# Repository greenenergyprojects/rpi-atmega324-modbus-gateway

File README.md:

# rpi-atmega324-modbus-gateway
Modbus Gateway for Raspberry PI

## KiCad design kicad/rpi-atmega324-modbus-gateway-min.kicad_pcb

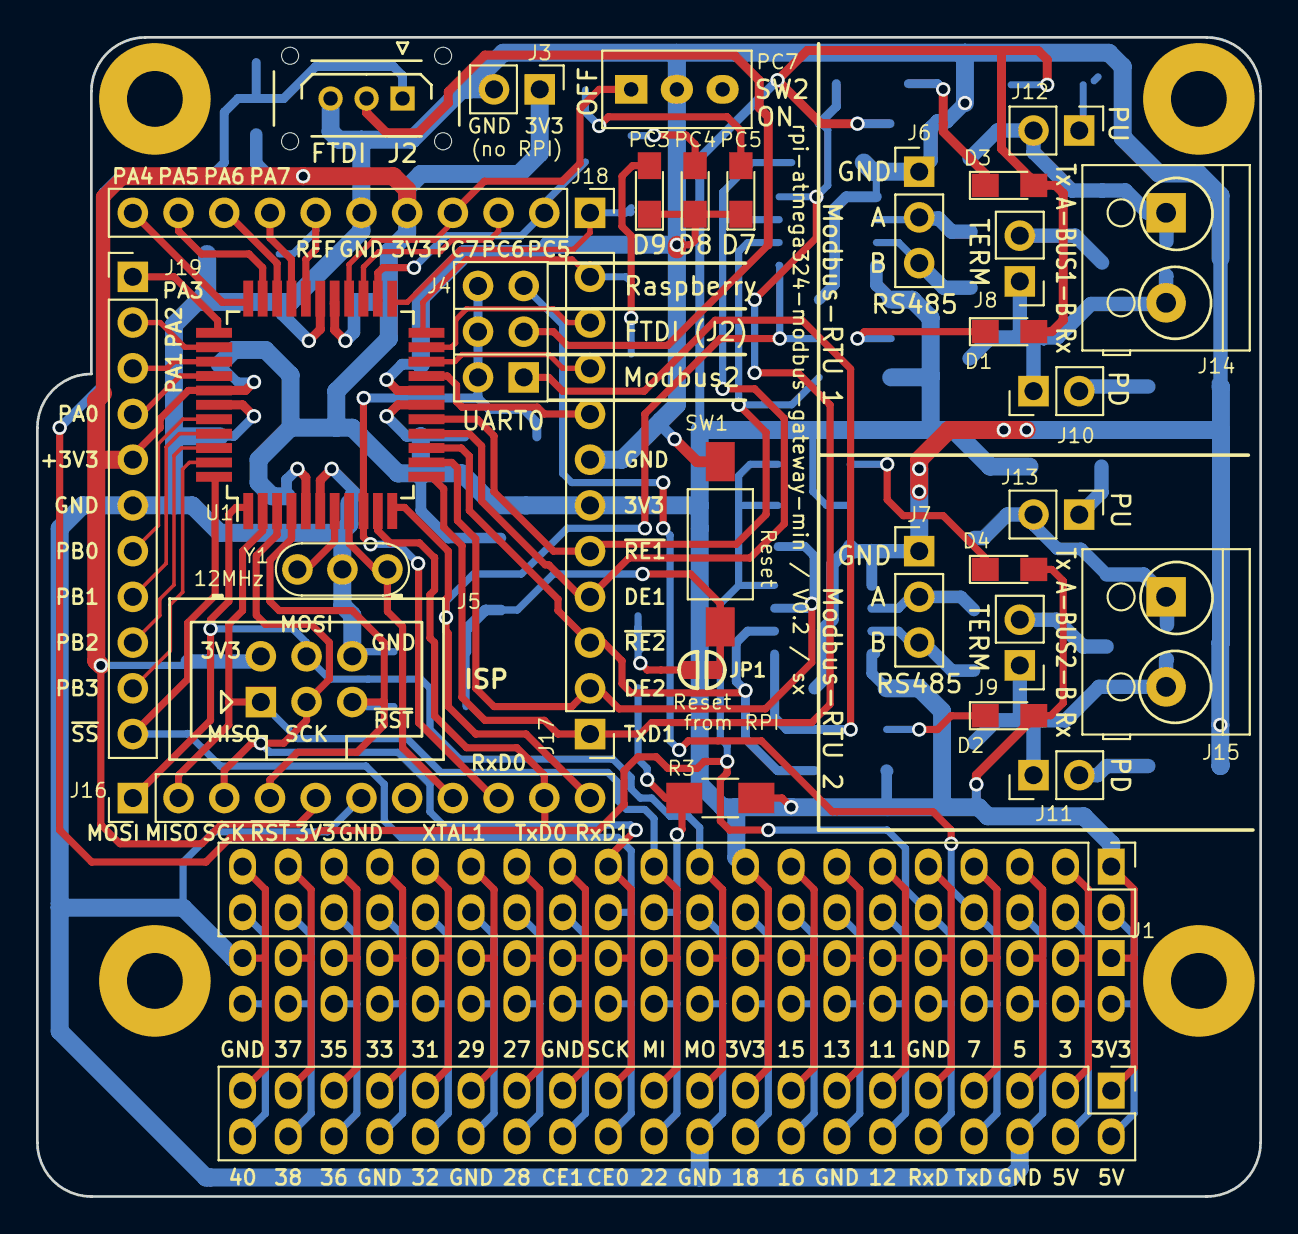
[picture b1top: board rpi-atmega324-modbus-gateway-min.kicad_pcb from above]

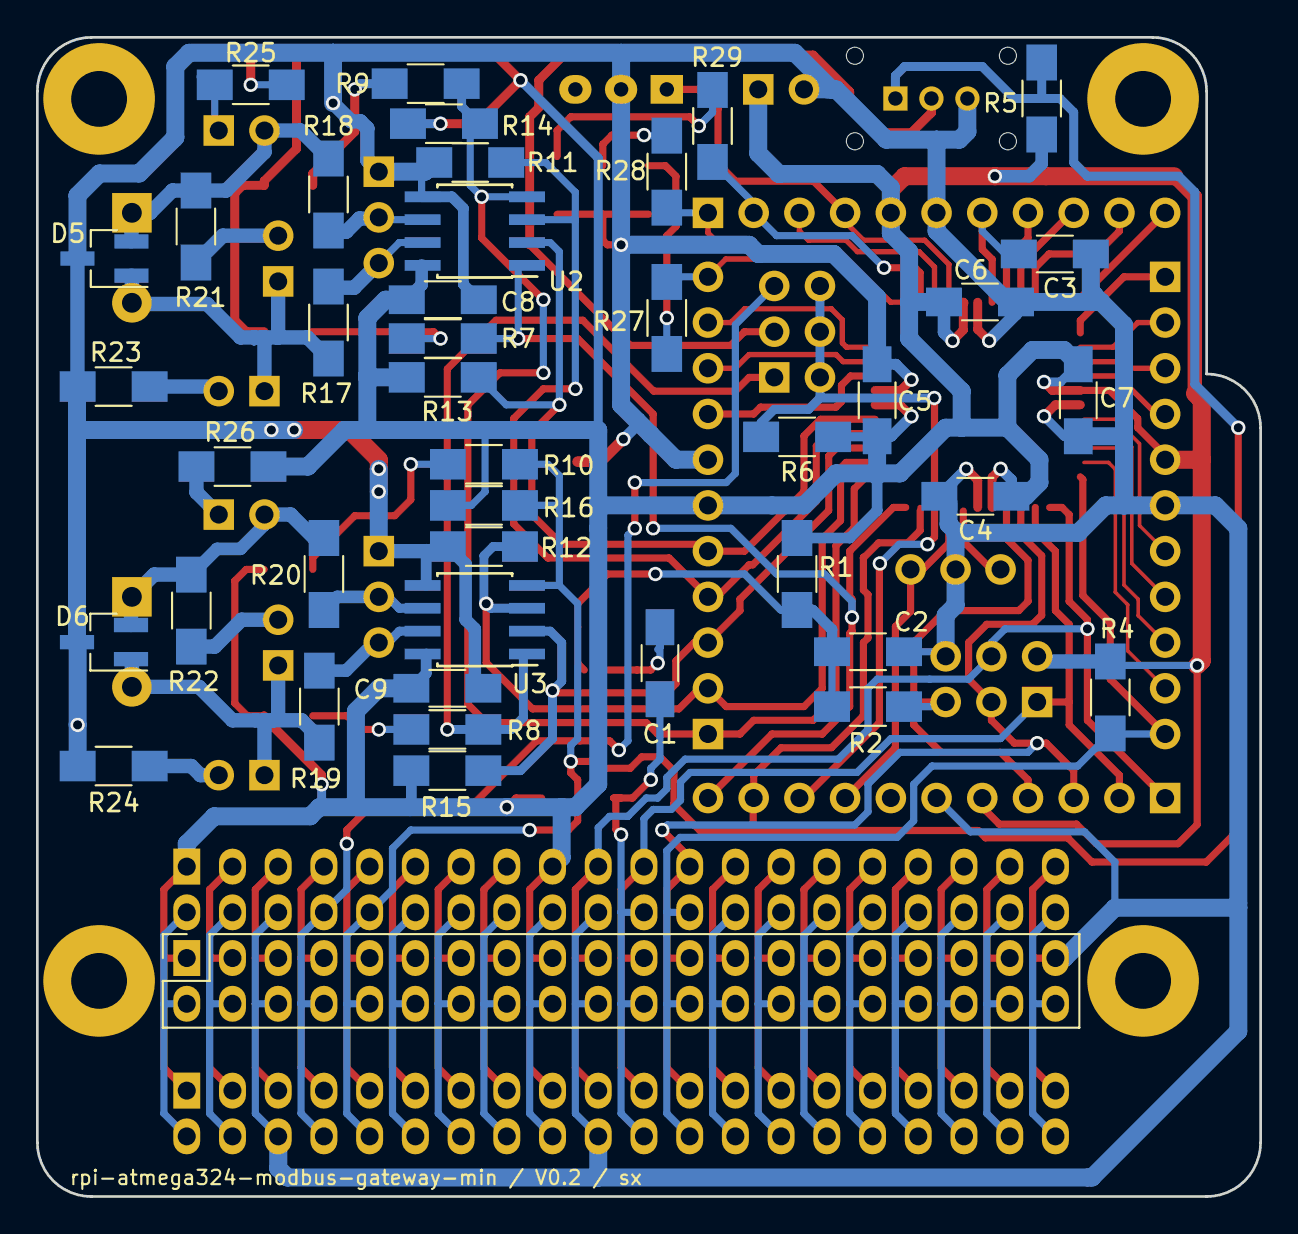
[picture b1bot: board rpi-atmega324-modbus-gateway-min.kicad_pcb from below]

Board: 2 copper layers, 68.0 x 64.4 mm, 73 parts (41 on the bottom side), 65 nets.

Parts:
C1, C3, C4, C5, C6, C7, C8, C9: 100n; C_1206_HandSoldering
C2: 1n; C_1206_HandSoldering
D1, D2, D3, D4, D7, D8, D9: LED; LED_0805_HandSoldering
D5, D6: D_TVS_x2_AAC; SOT-23_Handsoldering
J1: Raspberry_Pi_2+; RPI_DINRAILBOX_4TE_72mmx91mm_DEBUG
J2: UART-Harwin3; Harwin_LTek-Male_03x2.00mm_Straight_StrainRelief
J3, J8, J9, J10, J11, J12, J13: Conn_01x02; Pin_Header_Straight_1x02_Pitch2.54mm
J4: Conn_02x03_Odd_Even; Jumper_3x_2x03_Pitch2.54mm
J5: Atmega-ISP-6; IDC_2x3x2.54mm_Straight
J6, J7: Conn_01x03; Pin_Header_Straight_1x03_Pitch2.54mm
J14, J15: Screw_Terminal_01x02; Terminalblock-2x-5mm
J16, J17, J18, J19: Conn_01x11; Pin_Header_Straight_1x11_Pitch2.54mm
JP1: Jumper_NC_Small; SOLDER-JUMPER_1-WAY
R1, R2: 10K; R_1206_HandSoldering
R3, R4, R5, R6, R11, R12, R13, R14, R15, R16: 47K; R_1206_HandSoldering
R7, R8, R9, R10, R27, R28, R29: 560R; R_1206_HandSoldering
R17, R18, R19, R20: 10R; R_1206_HandSoldering
R21, R22: 150R; R_1206_HandSoldering
R23, R24, R25, R26: 330R; R_1206_HandSoldering
SW1: SW_Push; SW_SPST_FSMSM
SW2: SW_SPST; SW-ebay-171865305033
U1: ATMEGA324P-20AU; TQFP-44_10x10mm_Pitch0.8mm_Handsolded
U2, U3: SN65HVD11; SOIC-8_3.9x4.9mm_Pitch1.27mm_Handsolded
Y1: 12MHz; Resonator-3pin_w7.0mm_h2.5mm

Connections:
+3V3: C4.2, C5.2, C6.2, C7.2, C8.2, C9.2, D1.2, D2.2, D3.2, D4.2, J1.1, J1.17, J3.1, J5.2, J16.5, J17.6, J18.5, J19.5, R1.2, R3.2, R4.2, R5.2, R6.2, R13.2, R14.2, R15.2, R16.2, R25.2, R26.2, U1.5, U1.17, U1.27, U1.38, U2.8, U3.8
/AREF: C3.1, J18.7, U1.29
/DE1: J17.4, R11.2, U1.15, U2.3
/DE2: J17.2, R12.2, U1.13, U3.3
/Modbus/B1-A: D5.2, J12.2, J14.1, R18.2, R21.1
/Modbus/B1-B: D5.1, J8.1, J10.1, J14.2, R17.2
/Modbus/B2-A: D6.2, J13.2, J15.1, R20.2, R22.1
/Modbus/B2-B: D6.1, J9.1, J11.1, J15.2, R19.2
/Modbus/TxD2: J4.1, R8.1, U3.1
/PA0: J19.4, U1.37
/PA1: J19.3, U1.36
/PA2: J19.2, U1.35
/PA3: J19.1, U1.34
/PA4: J18.11, U1.33
/PA5: J18.10, U1.32
/PA6: J18.9, U1.31
/PA7: J18.8, U1.30
/PB0: J19.7, U1.40
/PB1: J19.8, U1.41
/PB2: J19.9, U1.42
/PB3: J19.10, U1.43
/PC0: J17.8, U1.19
/PC1: J17.9, U1.20
/PC2: J17.10, U1.21
/PC3: J17.11, R27.1, U1.22
/PC4: J18.1, R28.1, U1.23
/PC5: J18.2, R29.1, U1.24
/PC6: J18.3, U1.25
/PC7: J18.4, SW2.1, U1.26
/RxD0: J4.2, J4.4, J4.6, J16.9, R6.1, U1.9
/RxD1: J16.11, R7.1, U1.11, U2.1
/TxD0: J1.10, J2.1, J16.10, R5.1, R10.1, R16.1, U1.10, U3.4
/TxD1: J17.1, R9.1, R14.1, U1.12, U2.4
/UC_MISO: J1.21, J5.1, J16.2, U1.2
/UC_MOSI: J1.19, J5.4, J16.1, U1.1
/UC_RST: J5.5, J16.4, R2.1, U1.4
/UC_SCK: J1.23, J5.3, J16.3, U1.3
/XTAL1: J16.8, U1.8, Y1.3
/XTAL2: U1.7, Y1.1
/nRE1: J17.5, R13.1, U1.16, U2.2
/nRE2: J17.3, R15.1, U1.14, U3.2
/nSS: J1.24, J19.11, R4.1, U1.44
GND: C2.2, C3.2, C4.1, C5.1, C6.1, C7.1, C8.1, C9.1, D5.3, D6.3, D7.1, D8.1, D9.1, J1.6, J1.20, J1.39, J2.3, J3.2, J5.6, J6.1, J7.1, J16.6, J17.7, J18.6, J19.6, R11.1, R12.1, R23.1, R24.1, SW1.1, SW2.2, U1.6, U1.18, U1.28, U1.39, U2.5, U3.5, Y1.2
unnamed: C1.1, JP1.1
unnamed: C1.2, J1.22, R3.1
unnamed: C2.1, JP1.2, R1.1, R2.2, SW1.2
unnamed: D1.1, R7.2
unnamed: D2.1, R8.2
unnamed: D3.1, R9.2
unnamed: D4.1, R10.2
unnamed: D7.2, R29.2
unnamed: D8.2, R28.2
unnamed: D9.2, R27.2
unnamed: J1.8, J4.5
unnamed: J2.2, J4.3
unnamed: J6.2, R18.1, U2.6
unnamed: J6.3, R17.1, U2.7
unnamed: J7.2, R20.1, U3.6
unnamed: J7.3, R19.1, U3.7
unnamed: J8.2, R21.2
unnamed: J9.2, R22.2
unnamed: J10.2, R23.2
unnamed: J11.2, R24.2
unnamed: J12.1, R25.1
unnamed: J13.1, R26.1

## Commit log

2018-08-07 Modbus-ASCII Modbus-RTU gateway, first test version
2018-08-16 nibe1155
2018-08-17 nibe1155 polling
2018-08-18 nibe1155 statistics
2018-08-20 nibe1155 heatpump controller first version
2018-08-22 nibe controller
2018-08-26 including Nibe1155
2018-08-28 controlling heat pump
2018-08-29 PCB (kicad) tapeout V0.1
2018-08-31 README.md finalized for V0.1
2018-08-31 V0.2 Tapeout
2018-11-19 rpi/hpc economy mode
2018-12-24 start new nibe1155 server
2022-03-15 test mode
2022-03-19 wip...
2022-03-23 fix differences to home-conttrol-old project
2022-03-29 bugfix on OFF
2022-04-12 continous refresh of outdoor temperature
2023-01-08 schedule.json
2023-02-08 udp-server added
2023-03-09 server V0.3.4 (udp broadcast)
